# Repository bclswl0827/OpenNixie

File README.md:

# OpenNixie

OpenNixie: Nixie Clock for everyone!

```
├── circuit: KiCad projects
├── firmware: MCU firmware source code
├── panel: Acrylic panel (top and bottom)
└── tools: Tools for time alignment
```

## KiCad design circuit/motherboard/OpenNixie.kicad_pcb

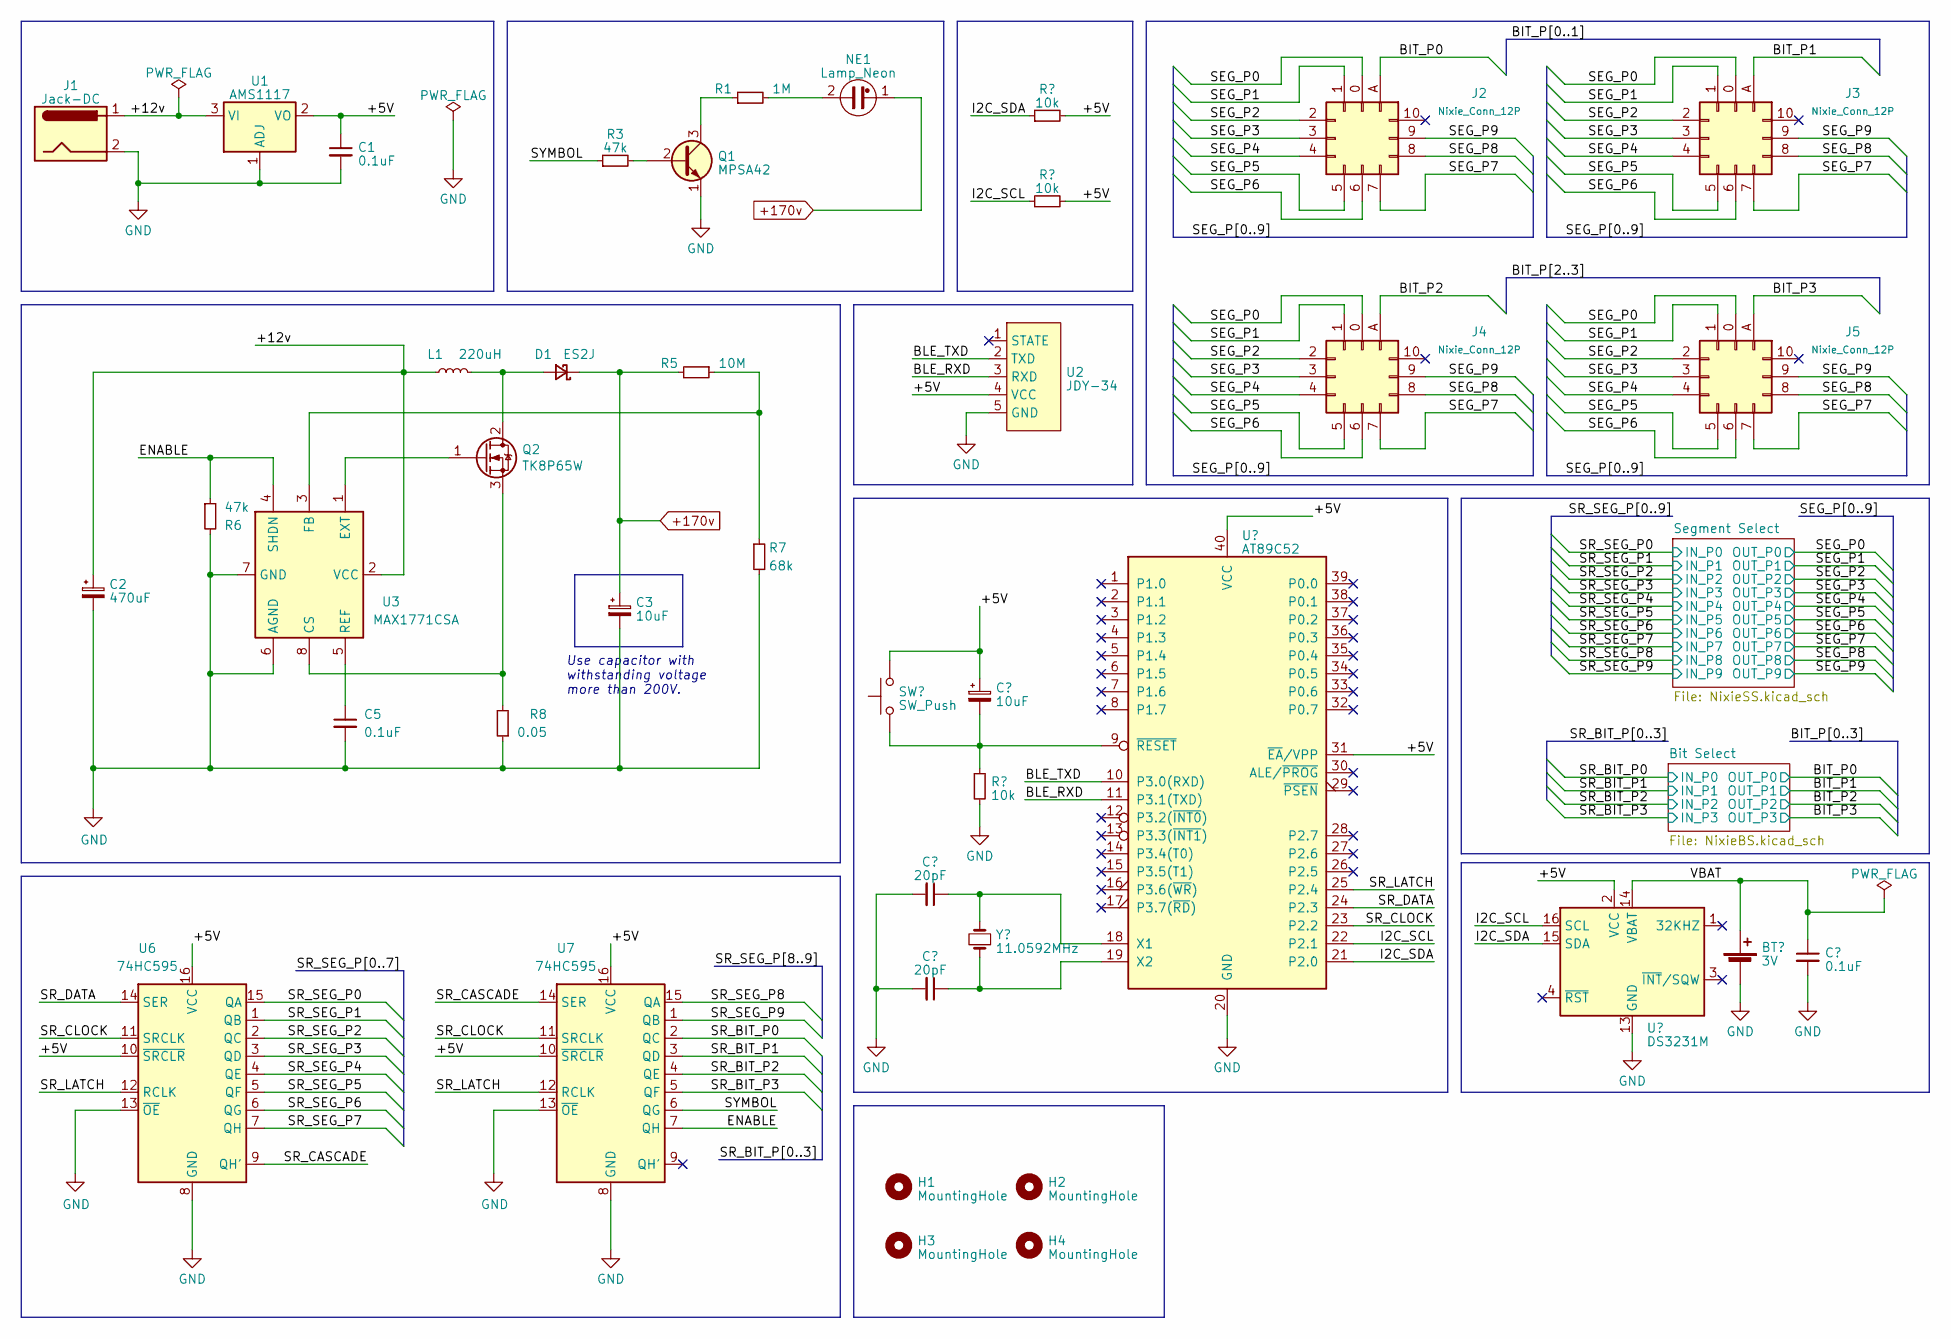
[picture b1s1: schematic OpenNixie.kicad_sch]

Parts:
BT1: 3V; BatteryHolder_LINX_BAT-HLD-012-SMT
C1, C5, C7: 0.1uF; C_Disc_D3.0mm_W2.0mm_P2.50mm
C2: 470uF; CP_Radial_D8.0mm_P3.50mm
C3: 10uF; CP_Radial_D8.0mm_P3.80mm
C4: 10uF; CP_Radial_D5.0mm_P2.50mm
C6, C8: 20pF; C_Disc_D3.0mm_W2.0mm_P2.50mm
D1: ES2J; D_SMA
H1, H2, H3, H4: MountingHole; MountingHole_3.2mm_M3
J1: Jack-DC; BarrelJack_Horizontal
J2, J3, J4, J5: Nixie_Conn_12P
L1: 220uH; L_Radial_D7.0mm_P3.00mm
NE1: Lamp_Neon; PinSocket_1x02_P2.54mm_Vertical
Q1: MPSA42; TO-92_Inline
Q2: TK8P65W; TO-252-2
R1: 1M; R_Axial_DIN0204_L3.6mm_D1.6mm_P7.62mm_Horizontal
R2, R4, R9: 10k; R_Axial_DIN0204_L3.6mm_D1.6mm_P7.62mm_Horizontal
R3, R6: 47k; R_Axial_DIN0204_L3.6mm_D1.6mm_P7.62mm_Horizontal
R5: 10M; R_Axial_DIN0204_L3.6mm_D1.6mm_P7.62mm_Horizontal
R7: 68k; R_Axial_DIN0204_L3.6mm_D1.6mm_P7.62mm_Horizontal
R8: 0.05; R_Axial_DIN0207_L6.3mm_D2.5mm_P10.16mm_Horizontal
SW1: SW_Push; SW_SPST_FSMSM
U1: AMS1117; SOT-223-3_TabPin2
U2: JDY-34; PinSocket_1x05_P2.54mm_Vertical
U3: MAX1771CSA; SO-8_3.9x4.9mm_P1.27mm
U4: AT89C52; DIP-40_W15.24mm
U5: DS3231M; SOIC-16W_7.5x10.3mm_P1.27mm
U6, U7: 74HC595; DIP-16_W7.62mm
Y1: 11.0592MHz; Crystal_HC18-U_Vertical

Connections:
+170v: C3.1, D1.1 (K), NE1.1, R5.2; also elsewhere on the board
/+5V: C1.1, C4.1, R2.2, R4.2, SW1.1, U1.2 (VO), U2.4 (VCC), U4.31 (~EA/VPP), U4.40 (VCC), U5.2 (VCC), U6.10 (~SRCLR), U6.16 (VCC), U7.10 (~SRCLR), U7.16 (VCC)
/+12v: C2.1, J1.1, L1.2, U1.3 (VI), U3.2 (VCC)
/BIT_P0: J2.A; also elsewhere on the board
/BIT_P1: J3.A; also elsewhere on the board
/BIT_P2: J4.A; also elsewhere on the board
/BIT_P3: J5.A; also elsewhere on the board
/BLE_RXD: U2.3 (RXD), U4.11 (P3.1(TXD))
/BLE_TXD: U2.2 (TXD), U4.10 (P3.0(RXD))
/ENABLE: R6.1, U3.4 (SHDN), U7.7 (QH)
/I2C_SCL: R4.1, U4.22 (P2.1), U5.16 (SCL)
/I2C_SDA: R2.1, U4.21 (P2.0), U5.15 (SDA)
/SEG_P0: J2.0, J3.0, J4.0, J5.0; also elsewhere on the board
/SEG_P1: J2.1, J3.1, J4.1, J5.1; also elsewhere on the board
/SEG_P2: J2.2, J3.2, J4.2, J5.2; also elsewhere on the board
/SEG_P3: J2.3, J3.3, J4.3, J5.3; also elsewhere on the board
/SEG_P4: J2.4, J3.4, J4.4, J5.4; also elsewhere on the board
/SEG_P5: J2.5, J3.5, J4.5, J5.5; also elsewhere on the board
/SEG_P6: J2.6, J3.6, J4.6, J5.6; also elsewhere on the board
/SEG_P7: J2.7, J3.7, J4.7, J5.7; also elsewhere on the board
/SEG_P8: J2.8, J3.8, J4.8, J5.8; also elsewhere on the board
/SEG_P9: J2.9, J3.9, J4.9, J5.9; also elsewhere on the board
/SR_BIT_P0: U7.2 (QC); also elsewhere on the board
/SR_BIT_P1: U7.3 (QD); also elsewhere on the board
/SR_BIT_P2: U7.4 (QE); also elsewhere on the board
/SR_BIT_P3: U7.5 (QF); also elsewhere on the board
/SR_CASCADE: U6.9 (QH'), U7.14 (SER)
/SR_CLOCK: U4.23 (P2.2), U6.11 (SRCLK), U7.11 (SRCLK)
/SR_DATA: U4.24 (P2.3), U6.14 (SER)
/SR_LATCH: U4.25 (P2.4), U6.12 (RCLK), U7.12 (RCLK)
/SR_SEG_P0: U6.15 (QA); also elsewhere on the board
/SR_SEG_P1: U6.1 (QB); also elsewhere on the board
/SR_SEG_P2: U6.2 (QC); also elsewhere on the board
/SR_SEG_P3: U6.3 (QD); also elsewhere on the board
/SR_SEG_P4: U6.4 (QE); also elsewhere on the board
/SR_SEG_P5: U6.5 (QF); also elsewhere on the board
/SR_SEG_P6: U6.6 (QG); also elsewhere on the board
/SR_SEG_P7: U6.7 (QH); also elsewhere on the board
/SR_SEG_P8: U7.15 (QA); also elsewhere on the board
/SR_SEG_P9: U7.1 (QB); also elsewhere on the board
/SYMBOL: R3.1, U7.6 (QG)
/VBAT: BT1.1 (+), C7.1, U5.14 (VBAT)
GND: BT1.2 (-), C1.2, C2.2, C3.2, C5.2, C6.2, C7.2, C8.2, J1.2, Q1.1 (E), R6.2, R7.2, R8.1, R9.2, U1.1 (ADJ), U2.5 (GND), U3.6 (AGND), U3.7 (GND), U4.20 (GND), U5.5 (GND), U5.6 (GND), U5.7 (GND), U5.8 (GND), U5.9 (GND), U5.10 (GND), U5.11 (GND), U5.12 (GND), U5.13 (GND), U6.8 (GND), U6.13 (~OE), U7.8 (GND), U7.13 (~OE); also elsewhere on the board
unnamed: D1.2 (A), L1.1, Q2.2 (D)
unnamed: NE1.2, R1.2
unnamed: Q1.2 (B), R3.2
unnamed: Q1.3 (C), R1.1
unnamed: Q2.1 (G), U3.1 (EXT)
unnamed: Q2.3 (S), R8.2, U3.8 (CS)
unnamed: R5.1, R7.1, U3.3 (FB)
unnamed: C5.1, U3.5 (REF)
unnamed: C6.1, U4.18 (X1), Y1.2
unnamed: C8.1, U4.19 (X2), Y1.1
unnamed: C4.2, R9.1, SW1.2, U4.9 (~RESET)

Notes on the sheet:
Use capacitor with withstanding voltage more than 200V.

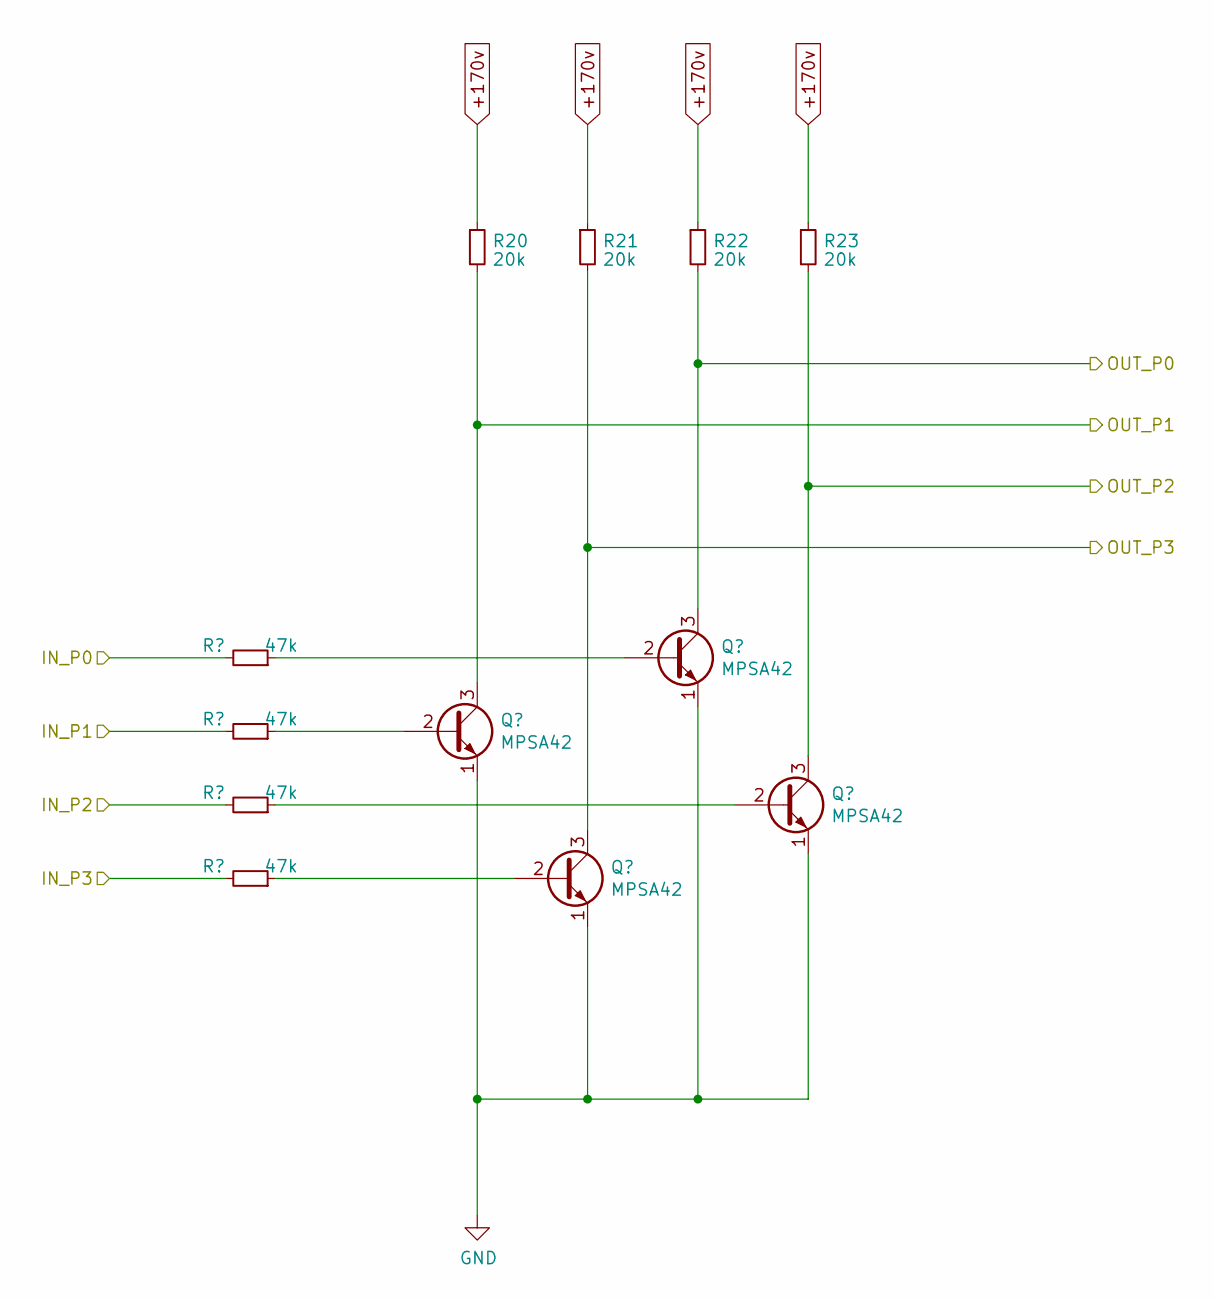
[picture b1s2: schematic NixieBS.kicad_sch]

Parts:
Q13, Q14, Q15, Q16: MPSA42; TO-92_Inline
R20, R21, R22, R23: 20k; R_Axial_DIN0207_L6.3mm_D2.5mm_P10.16mm_Horizontal
R24, R25, R26, R27: 47k; R_Axial_DIN0204_L3.6mm_D1.6mm_P7.62mm_Horizontal

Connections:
+170v: R20.1, R21.1, R22.1, R23.1; also elsewhere on the board
/BIT_P0: Q13.3 (C), R22.2; also elsewhere on the board
/BIT_P1: Q14.3 (C), R20.2; also elsewhere on the board
/BIT_P2: Q15.3 (C), R23.2; also elsewhere on the board
/BIT_P3: Q16.3 (C), R21.2; also elsewhere on the board
/SR_BIT_P0: R24.2; also elsewhere on the board
/SR_BIT_P1: R25.2; also elsewhere on the board
/SR_BIT_P2: R26.2; also elsewhere on the board
/SR_BIT_P3: R27.2; also elsewhere on the board
GND: Q13.1 (E), Q14.1 (E), Q15.1 (E), Q16.1 (E); also elsewhere on the board
unnamed: Q13.2 (B), R24.1
unnamed: Q14.2 (B), R25.1
unnamed: Q15.2 (B), R26.1
unnamed: Q16.2 (B), R27.1

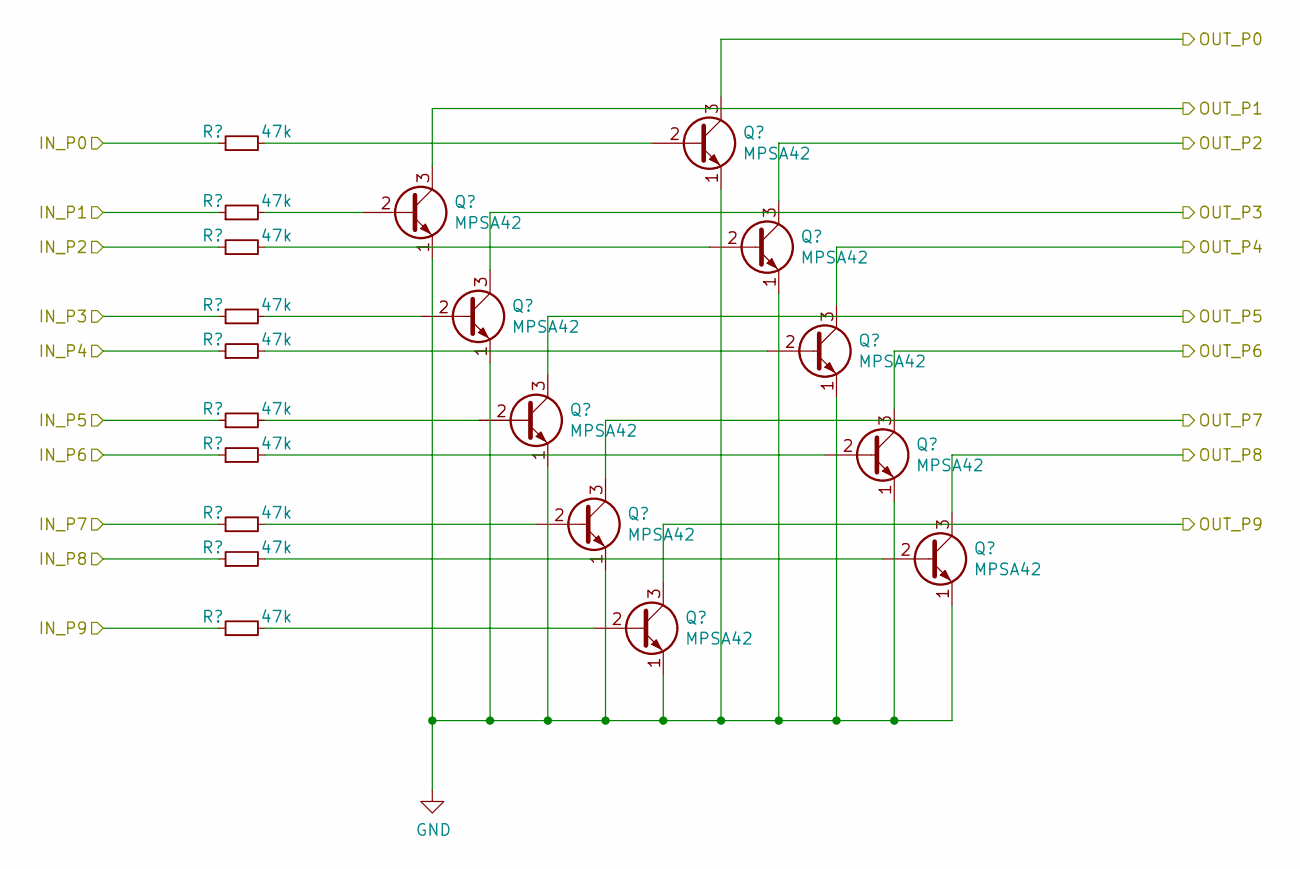
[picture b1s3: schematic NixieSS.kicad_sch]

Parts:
Q3, Q4, Q5, Q6, Q7, Q8, Q9, Q10, Q11, Q12: MPSA42; TO-92_Inline
R10, R11, R12, R13, R14, R15, R16, R17, R18, R19: 47k; R_Axial_DIN0204_L3.6mm_D1.6mm_P7.62mm_Horizontal

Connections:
/SEG_P0: Q3.3 (C); also elsewhere on the board
/SEG_P1: Q4.3 (C); also elsewhere on the board
/SEG_P2: Q5.3 (C); also elsewhere on the board
/SEG_P3: Q6.3 (C); also elsewhere on the board
/SEG_P4: Q7.3 (C); also elsewhere on the board
/SEG_P5: Q8.3 (C); also elsewhere on the board
/SEG_P6: Q9.3 (C); also elsewhere on the board
/SEG_P7: Q10.3 (C); also elsewhere on the board
/SEG_P8: Q11.3 (C); also elsewhere on the board
/SEG_P9: Q12.3 (C); also elsewhere on the board
/SR_SEG_P0: R10.1; also elsewhere on the board
/SR_SEG_P1: R11.1; also elsewhere on the board
/SR_SEG_P2: R12.1; also elsewhere on the board
/SR_SEG_P3: R13.1; also elsewhere on the board
/SR_SEG_P4: R14.1; also elsewhere on the board
/SR_SEG_P5: R15.1; also elsewhere on the board
/SR_SEG_P6: R16.1; also elsewhere on the board
/SR_SEG_P7: R17.1; also elsewhere on the board
/SR_SEG_P8: R18.1; also elsewhere on the board
/SR_SEG_P9: R19.1; also elsewhere on the board
GND: Q3.1 (E), Q4.1 (E), Q5.1 (E), Q6.1 (E), Q7.1 (E), Q8.1 (E), Q9.1 (E), Q10.1 (E), Q11.1 (E), Q12.1 (E); also elsewhere on the board
unnamed: Q3.2 (B), R10.2
unnamed: Q4.2 (B), R11.2
unnamed: Q5.2 (B), R12.2
unnamed: Q6.2 (B), R13.2
unnamed: Q7.2 (B), R14.2
unnamed: Q8.2 (B), R15.2
unnamed: Q9.2 (B), R16.2
unnamed: Q10.2 (B), R17.2
unnamed: Q11.2 (B), R18.2
unnamed: Q12.2 (B), R19.2

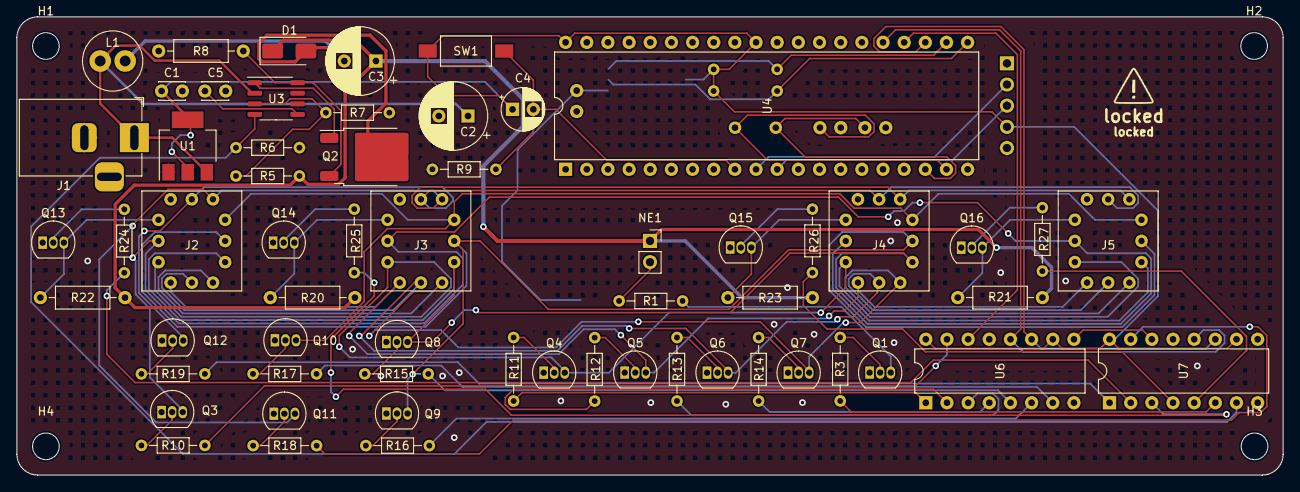
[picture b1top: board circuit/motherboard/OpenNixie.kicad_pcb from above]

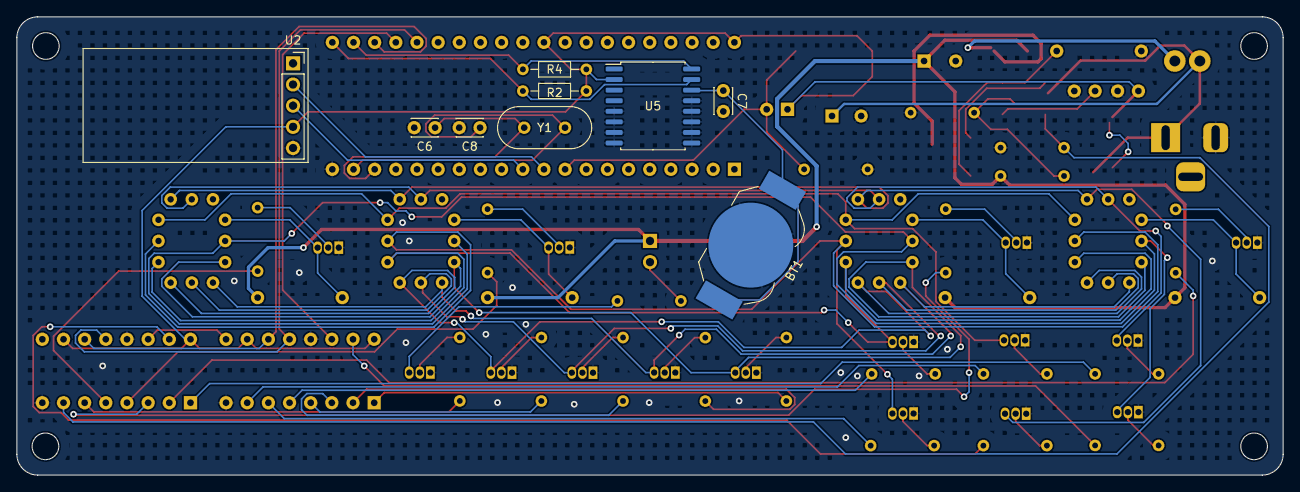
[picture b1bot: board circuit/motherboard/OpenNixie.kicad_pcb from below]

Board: 2 copper layers, 152.0 x 55.0 mm, 73 parts (9 on the bottom side), 68 nets.

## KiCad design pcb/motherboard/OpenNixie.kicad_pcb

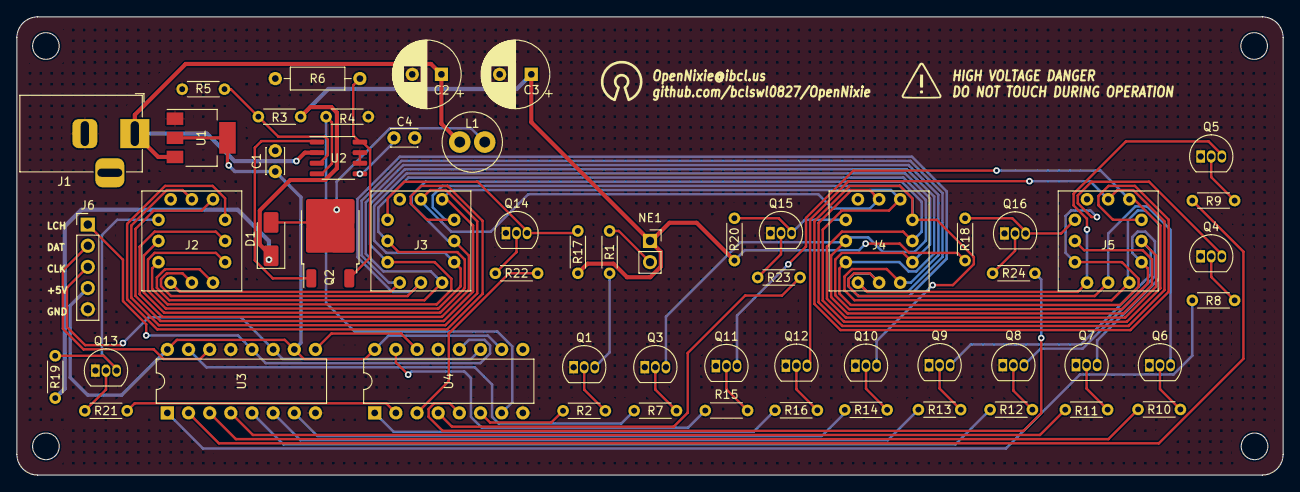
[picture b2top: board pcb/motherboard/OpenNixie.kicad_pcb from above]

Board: 2 copper layers, 152.0 x 55.0 mm, 61 parts (0 on the bottom side), 60 nets.

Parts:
C1, C4: 0.1uF; C_Disc_D3.0mm_W2.0mm_P2.50mm
C2: 470uF; CP_Radial_D8.0mm_P3.50mm
C3: 10uF; CP_Radial_D8.0mm_P3.80mm
D1: ES2J; D_SMA
H1, H2, H3, H4: MountingHole; MountingHole_3.2mm_M3
J1: Jack-DC; BarrelJack_Horizontal
J2, J3, J4, J5: Nixie_Conn_12P
J6: Conn_01x05; PinHeader_1x05_P2.54mm_Vertical
L1: 220uH; L_Radial_D7.0mm_P3.00mm
NE1: Lamp_Neon; PinSocket_1x02_P2.54mm_Vertical
Q1, Q3, Q4, Q5, Q6, Q7, Q8, Q9, Q10, Q11, Q12, Q13, Q14, Q15, Q16: MPSA42; TO-92_Inline
Q2: TK8P65W; TO-252-2
R1: 1M; R_Axial_DIN0204_L3.6mm_D1.6mm_P5.08mm_Horizontal
R2, R4, R7, R8, R9, R10, R11, R12, R13, R14, R15, R16, R17, R18, R19, R20, R21, R22, R23, R24: 47k; R_Axial_DIN0204_L3.6mm_D1.6mm_P5.08mm_Horizontal
R3: 10M; R_Axial_DIN0204_L3.6mm_D1.6mm_P5.08mm_Horizontal
R5: 68k; R_Axial_DIN0204_L3.6mm_D1.6mm_P5.08mm_Horizontal
R6: 0.05; R_Axial_DIN0207_L6.3mm_D2.5mm_P10.16mm_Horizontal
U1: AMS1117; SOT-223-3_TabPin2
U2: MAX1771CSA; SO-8_3.9x4.9mm_P1.27mm
U3, U4: 74HC595; DIP-16_W7.62mm

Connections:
+170v: C3.1, D1.1 (K), NE1.1, R3.2, R17.1, R18.1, R19.1, R20.1
/+5v: C1.1, J6.4, U1.2 (VO), U3.10 (~SRCLR), U3.16 (VCC), U4.10 (~SRCLR), U4.16 (VCC)
/+12v: C2.1, J1.1, L1.2, U1.3 (VI), U2.2 (VCC)
/BIT_P0: J2.A, Q13.3 (C), R19.2
/BIT_P1: J3.A, Q14.3 (C), R17.2
/BIT_P2: J4.A, Q15.3 (C), R20.2
/BIT_P3: J5.A, Q16.3 (C), R18.2
/ENABLE: R4.1, U2.4 (SHDN), U4.7 (QH)
/SEG_P0: J2.0, J3.0, J4.0, J5.0, Q3.3 (C)
/SEG_P1: J2.1, J3.1, J4.1, J5.1, Q4.3 (C)
/SEG_P2: J2.2, J3.2, J4.2, J5.2, Q5.3 (C)
/SEG_P3: J2.3, J3.3, J4.3, J5.3, Q6.3 (C)
/SEG_P4: J2.4, J3.4, J4.4, J5.4, Q7.3 (C)
/SEG_P5: J2.5, J3.5, J4.5, J5.5, Q8.3 (C)
/SEG_P6: J2.6, J3.6, J4.6, J5.6, Q9.3 (C)
/SEG_P7: J2.7, J3.7, J4.7, J5.7, Q10.3 (C)
/SEG_P8: J2.8, J3.8, J4.8, J5.8, Q11.3 (C)
/SEG_P9: J2.9, J3.9, J4.9, J5.9, Q12.3 (C)
/SR_BIT_P0: R21.2, U4.2 (QC)
/SR_BIT_P1: R22.2, U4.3 (QD)
/SR_BIT_P2: R23.2, U4.4 (QE)
/SR_BIT_P3: R24.2, U4.5 (QF)
/SR_CASCADE: U3.9 (QH'), U4.14 (SER)
/SR_CLOCK: J6.3, U3.11 (SRCLK), U4.11 (SRCLK)
/SR_DATA: J6.2, U3.14 (SER)
/SR_LATCH: J6.1, U3.12 (RCLK), U4.12 (RCLK)
/SR_SEG_P0: R7.1, U3.15 (QA)
/SR_SEG_P1: R8.1, U3.1 (QB)
/SR_SEG_P2: R9.1, U3.2 (QC)
/SR_SEG_P3: R10.1, U3.3 (QD)
/SR_SEG_P4: R11.1, U3.4 (QE)
/SR_SEG_P5: R12.1, U3.5 (QF)
/SR_SEG_P6: R13.1, U3.6 (QG)
/SR_SEG_P7: R14.1, U3.7 (QH)
/SR_SEG_P8: R15.1, U4.15 (QA)
/SR_SEG_P9: R16.1, U4.1 (QB)
/SYMBOL: R2.1, U4.6 (QG)
GND: C1.2, C2.2, C3.2, C4.2, J1.2, J6.5, Q1.1 (E), Q3.1 (E), Q4.1 (E), Q5.1 (E), Q6.1 (E), Q7.1 (E), Q8.1 (E), Q9.1 (E), Q10.1 (E), Q11.1 (E), Q12.1 (E), Q13.1 (E), Q14.1 (E), Q15.1 (E), Q16.1 (E), R4.2, R5.2, R6.1, U1.1 (ADJ), U2.6 (AGND), U2.7 (GND), U3.8 (GND), U3.13 (~OE), U4.8 (GND), U4.13 (~OE)
unnamed: D1.2 (A), L1.1, Q2.2 (D)
unnamed: NE1.2, R1.2
unnamed: Q1.2 (B), R2.2
unnamed: Q1.3 (C), R1.1
unnamed: Q2.1 (G), U2.1 (EXT)
unnamed: Q2.3 (S), R6.2, U2.8 (CS)
unnamed: Q3.2 (B), R7.2
unnamed: Q4.2 (B), R8.2
unnamed: Q5.2 (B), R9.2
unnamed: Q6.2 (B), R10.2
unnamed: Q7.2 (B), R11.2
unnamed: Q8.2 (B), R12.2
unnamed: Q9.2 (B), R13.2
unnamed: Q10.2 (B), R14.2
unnamed: Q11.2 (B), R15.2
unnamed: Q12.2 (B), R16.2
unnamed: Q13.2 (B), R21.1
unnamed: Q14.2 (B), R22.1
unnamed: Q15.2 (B), R23.1
unnamed: Q16.2 (B), R24.1
unnamed: R3.1, R5.1, U2.3 (FB)
unnamed: C4.1, U2.5 (REF)

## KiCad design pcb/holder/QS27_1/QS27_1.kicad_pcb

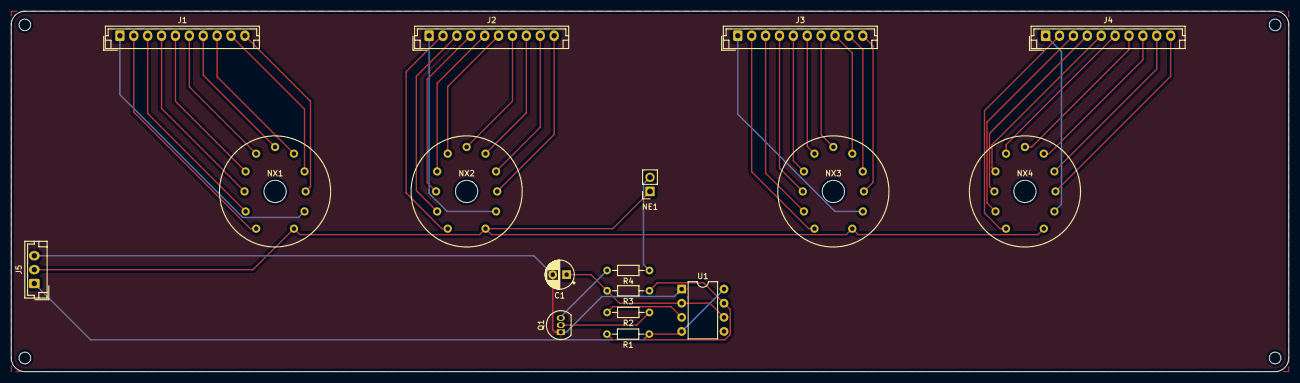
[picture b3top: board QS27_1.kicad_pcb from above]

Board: 2 copper layers, 229.9 x 64.9 mm, 17 parts (0 on the bottom side), 49 nets.

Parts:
C1: 10uF; CP_Radial_D5.0mm_P2.50mm
J1, J2, J3, J4: Conn_01x10; JST_EH_B10B-EH-A_1x10_P2.50mm_Vertical
J5: Conn_01x03; JST_EH_B3B-EH-A_1x03_P2.50mm_Vertical
NE1: Lamp_Neon; PinSocket_1x02_P2.54mm_Vertical
NX1, NX2, NX3, NX4: QS27-1
Q1: MPSA42; TO-92_Inline
R1: 1k; R_Axial_DIN0204_L3.6mm_D1.6mm_P7.62mm_Horizontal
R2: 10k; R_Axial_DIN0204_L3.6mm_D1.6mm_P7.62mm_Horizontal
R3, R4: 100k; R_Axial_DIN0204_L3.6mm_D1.6mm_P7.62mm_Horizontal
U1: NE555P; DIP-8_W7.62mm

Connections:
+5V: J5.1, R1.1, U1.4, U1.8
ANODE_PIN: J5.2, NE1.1, NX1.A, NX2.A, NX3.A, NX4.A
GND: C1.2, J5.3, Q1.1, U1.1
NE555_OUT: Q1.2, R2.1
unnamed: C1.1, R3.2, U1.2, U1.6
unnamed: J1.1, NX1.0
unnamed: J1.2, NX1.1
unnamed: J1.3, NX1.2
unnamed: J1.4, NX1.3
unnamed: J1.5, NX1.4
unnamed: J1.6, NX1.5
unnamed: J1.7, NX1.6
unnamed: J1.8, NX1.7
unnamed: J1.9, NX1.8
unnamed: J1.10, NX1.9
unnamed: J2.1, NX2.0
unnamed: J2.2, NX2.1
unnamed: J2.3, NX2.2
unnamed: J2.4, NX2.3
unnamed: J2.5, NX2.4
unnamed: J2.6, NX2.5
unnamed: J2.7, NX2.6
unnamed: J2.8, NX2.7
unnamed: J2.9, NX2.8
unnamed: J2.10, NX2.9
unnamed: J3.1, NX3.0
unnamed: J3.2, NX3.1
unnamed: J3.3, NX3.2
unnamed: J3.4, NX3.3
unnamed: J3.5, NX3.4
unnamed: J3.6, NX3.5
unnamed: J3.7, NX3.6
unnamed: J3.8, NX3.7
unnamed: J3.9, NX3.8
unnamed: J3.10, NX3.9
unnamed: J4.1, NX4.0
unnamed: J4.2, NX4.1
unnamed: J4.3, NX4.2
unnamed: J4.4, NX4.3
unnamed: J4.5, NX4.4
unnamed: J4.6, NX4.5
unnamed: J4.7, NX4.6
unnamed: J4.8, NX4.7
unnamed: J4.9, NX4.8
unnamed: J4.10, NX4.9
unnamed: NE1.2, R4.1
unnamed: Q1.3, R4.2
unnamed: R1.2, R3.1, U1.7
unnamed: R2.2, U1.3
